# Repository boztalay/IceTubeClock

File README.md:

IceTubeClock
============

A clock with ice tubes for its display

Milling the enclosure:

Milling the base PCB:

Drilling the base PCB:

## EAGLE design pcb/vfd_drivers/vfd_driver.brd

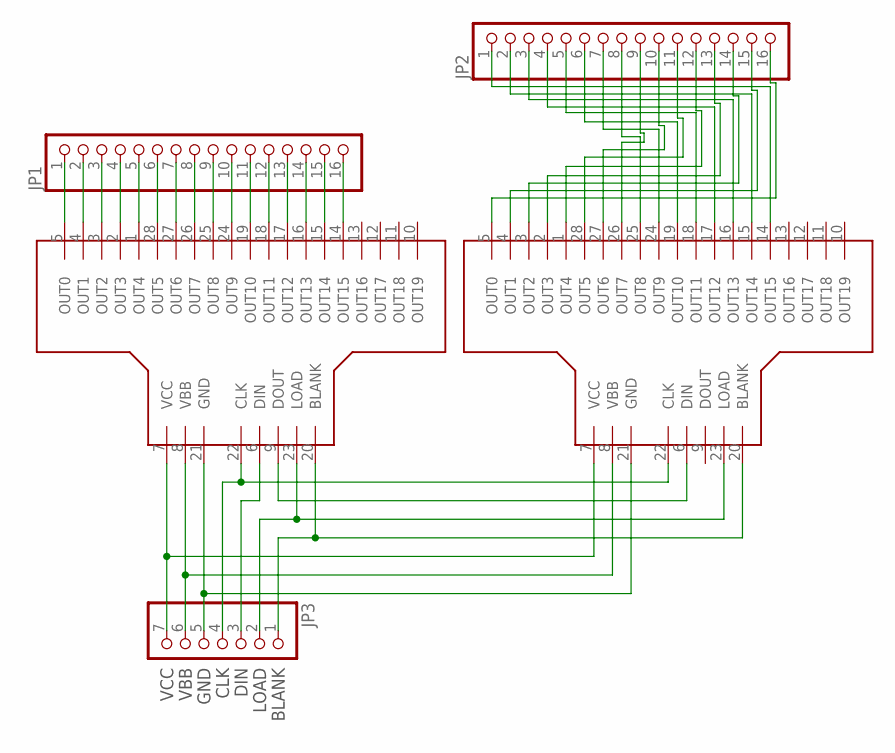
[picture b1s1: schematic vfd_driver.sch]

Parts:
JP1, JP2: PINHD-1X16; 1X16
JP3: PINHD-1X7; 1X07
U$1, U$2: MAX6921/31; TSSOP-28

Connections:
BLANK: JP3.1, U$1.20 (BLANK), U$2.20 (BLANK)
CLK: JP3.4, U$1.22 (CLK), U$2.22 (CLK)
DIN: JP3.3, U$1.6 (DIN)
DINOUT: U$1.9 (DOUT), U$2.6 (DIN)
GND: JP3.5, U$1.21 (GND), U$2.21 (GND)
LOAD: JP3.2, U$1.23 (LOAD), U$2.23 (LOAD)
unnamed: JP2.1, U$2.14 (OUT15)
unnamed: JP2.2, U$2.15 (OUT14)
unnamed: JP2.3, U$2.16 (OUT13)
unnamed: JP2.4, U$2.17 (OUT12)
unnamed: JP2.5, U$2.18 (OUT11)
unnamed: JP2.6, U$2.19 (OUT10)
unnamed: JP2.7, U$2.24 (OUT9)
unnamed: JP2.8, U$2.25 (OUT8)
unnamed: JP2.9, U$2.26 (OUT7)
unnamed: JP2.10, U$2.27 (OUT6)
unnamed: JP2.11, U$2.28 (OUT5)
unnamed: JP2.12, U$2.1 (OUT4)
unnamed: JP2.13, U$2.2 (OUT3)
unnamed: JP2.14, U$2.3 (OUT2)
unnamed: JP2.15, U$2.4 (OUT1)
unnamed: JP2.16, U$2.5 (OUT0)
unnamed: JP1.16, U$1.14 (OUT15)
unnamed: JP1.15, U$1.15 (OUT14)
unnamed: JP1.14, U$1.16 (OUT13)
unnamed: JP1.13, U$1.17 (OUT12)
unnamed: JP1.12, U$1.18 (OUT11)
unnamed: JP1.11, U$1.19 (OUT10)
unnamed: JP1.10, U$1.24 (OUT9)
unnamed: JP1.9, U$1.25 (OUT8)
unnamed: JP1.8, U$1.26 (OUT7)
unnamed: JP1.7, U$1.27 (OUT6)
unnamed: JP1.6, U$1.28 (OUT5)
unnamed: JP1.5, U$1.1 (OUT4)
unnamed: JP1.4, U$1.2 (OUT3)
unnamed: JP1.3, U$1.3 (OUT2)
unnamed: JP1.2, U$1.4 (OUT1)
unnamed: JP1.1, U$1.5 (OUT0)
VBB: JP3.6, U$1.8 (VBB), U$2.8 (VBB)
VCC: JP3.7, U$1.7 (VCC), U$2.7 (VCC)

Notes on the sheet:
VCC
VBB
GND
CLK
DIN
LOAD
BLANK

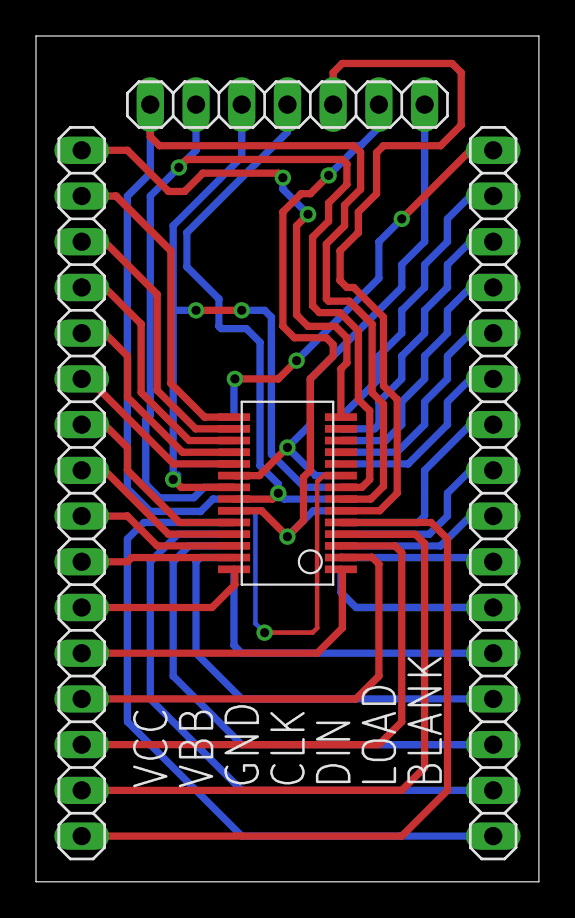
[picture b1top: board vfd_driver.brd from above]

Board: 2 copper layers, 27.9 x 47.0 mm, 5 parts (1 on the bottom side), 40 nets.

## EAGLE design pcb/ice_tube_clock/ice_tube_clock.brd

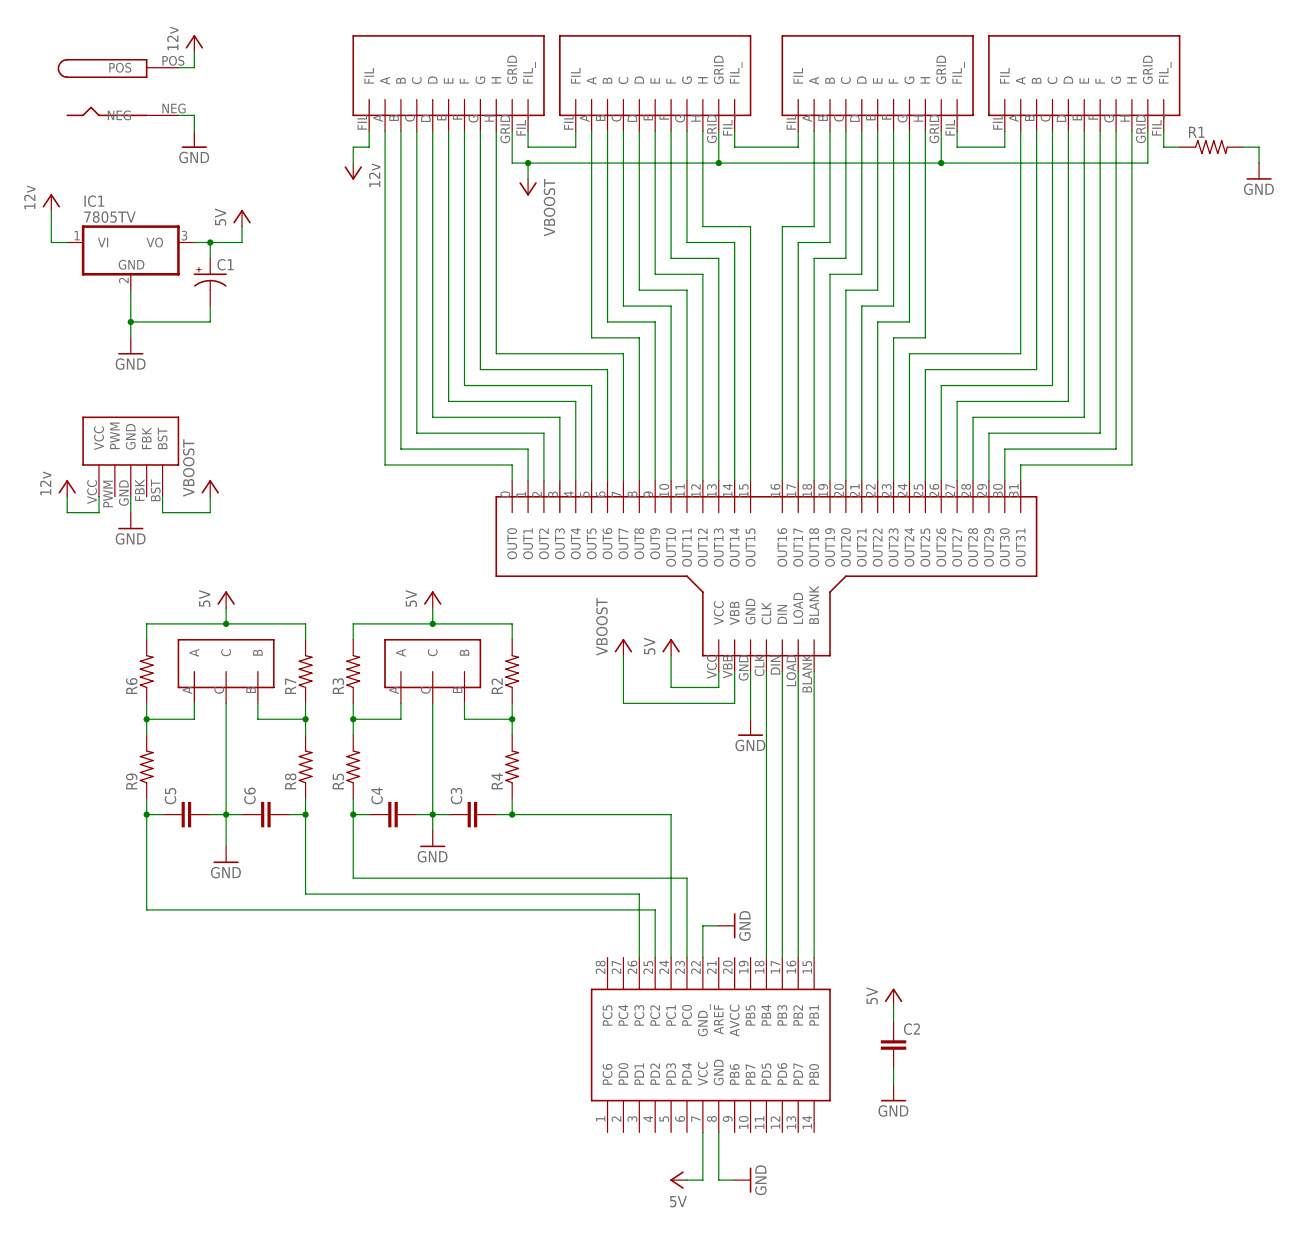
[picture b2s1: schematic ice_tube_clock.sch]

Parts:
C1: CAP_POLPTH1; CPOL-RADIAL-100UF-25V
C2, C3, C4, C5, C6: 0.1UF-50V-20%(PTH)KIT-EZ; CAP-PTH-SMALL-KIT
IC1: 7805TV; TO220V
R1, R2, R3, R4, R5, R6, R7, R8, R9: R-US_0204/7; 0204/7
U$1: ATMEGA168-DIP28; DIP28
U$2: IV11-BOOST-SUPPLY
U$3, U$4, U$5, U$6: IV-11-CARRIER
U$7: PJ-037A
U$8: VFD-DRIVER-CARRIER
U$9, U$10: PEL12S

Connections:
+5V: C1.1 (+), C2.1, IC1.3 (VO), R2.2, R3.2, R6.2, R7.2, U$1.7 (VCC), U$8.VCC
+12V: IC1.1 (VI), U$2.VCC, U$3.FIL, U$7.POS
ET: C4.1, R5.1, U$1.23 (PC0)
GND: C1.2 (-), C2.2, C3.1, C4.2, C5.2, C6.1, IC1.2 (GND), R1.2, U$1.8 (GND), U$1.22 (GND_), U$2.GND, U$7.NEG, U$8.GND, U$9.C, U$10.C
unnamed: U$3.FIL_, U$4.FIL
unnamed: U$4.FIL_, U$5.FIL
unnamed: U$5.FIL_, U$6.FIL
unnamed: U$3.A, U$8.0 (OUT0)
unnamed: U$3.B, U$8.1 (OUT1)
unnamed: U$3.C, U$8.2 (OUT2)
unnamed: U$3.D, U$8.3 (OUT3)
unnamed: U$3.E, U$8.4 (OUT4)
unnamed: U$3.F, U$8.5 (OUT5)
unnamed: U$3.G, U$8.6 (OUT6)
unnamed: U$3.H, U$8.7 (OUT7)
unnamed: U$4.A, U$8.8 (OUT8)
unnamed: U$4.B, U$8.9 (OUT9)
unnamed: U$4.C, U$8.10 (OUT10)
unnamed: U$4.D, U$8.11 (OUT11)
unnamed: U$4.E, U$8.12 (OUT12)
unnamed: U$4.F, U$8.13 (OUT13)
unnamed: U$4.G, U$8.14 (OUT14)
unnamed: U$4.H, U$8.15 (OUT15)
unnamed: U$6.H, U$8.31 (OUT31)
unnamed: U$6.G, U$8.30 (OUT30)
unnamed: U$6.F, U$8.29 (OUT29)
unnamed: U$6.E, U$8.28 (OUT28)
unnamed: U$6.D, U$8.27 (OUT27)
unnamed: U$6.C, U$8.26 (OUT26)
unnamed: U$6.B, U$8.25 (OUT25)
unnamed: U$6.A, U$8.24 (OUT24)
unnamed: U$5.H, U$8.23 (OUT23)
unnamed: U$5.G, U$8.22 (OUT22)
unnamed: U$5.F, U$8.21 (OUT21)
unnamed: U$5.E, U$8.20 (OUT20)
unnamed: U$5.D, U$8.19 (OUT19)
unnamed: U$5.C, U$8.18 (OUT18)
unnamed: U$5.B, U$8.17 (OUT17)
unnamed: U$5.A, U$8.16 (OUT16)
unnamed: R1.1, U$6.FIL_
unnamed: U$1.15 (PB1), U$8.BLANK
unnamed: U$1.16 (PB2), U$8.LOAD
unnamed: U$1.17 (PB3), U$8.DIN
unnamed: U$1.18 (PB4), U$8.CLK
unnamed: C3.2, R4.1, U$1.24 (PC1)
unnamed: R3.1, R5.2, U$10.A
unnamed: R6.1, R9.2, U$9.A
unnamed: R7.1, R8.2, U$9.B
unnamed: R2.1, R4.2, U$10.B
unnamed: C5.1, R9.1, U$1.25 (PC2)
unnamed: C6.2, R8.1, U$1.26 (PC3)
VBOOST: U$2.BST, U$3.GRID, U$4.GRID, U$5.GRID, U$6.GRID, U$8.VBB

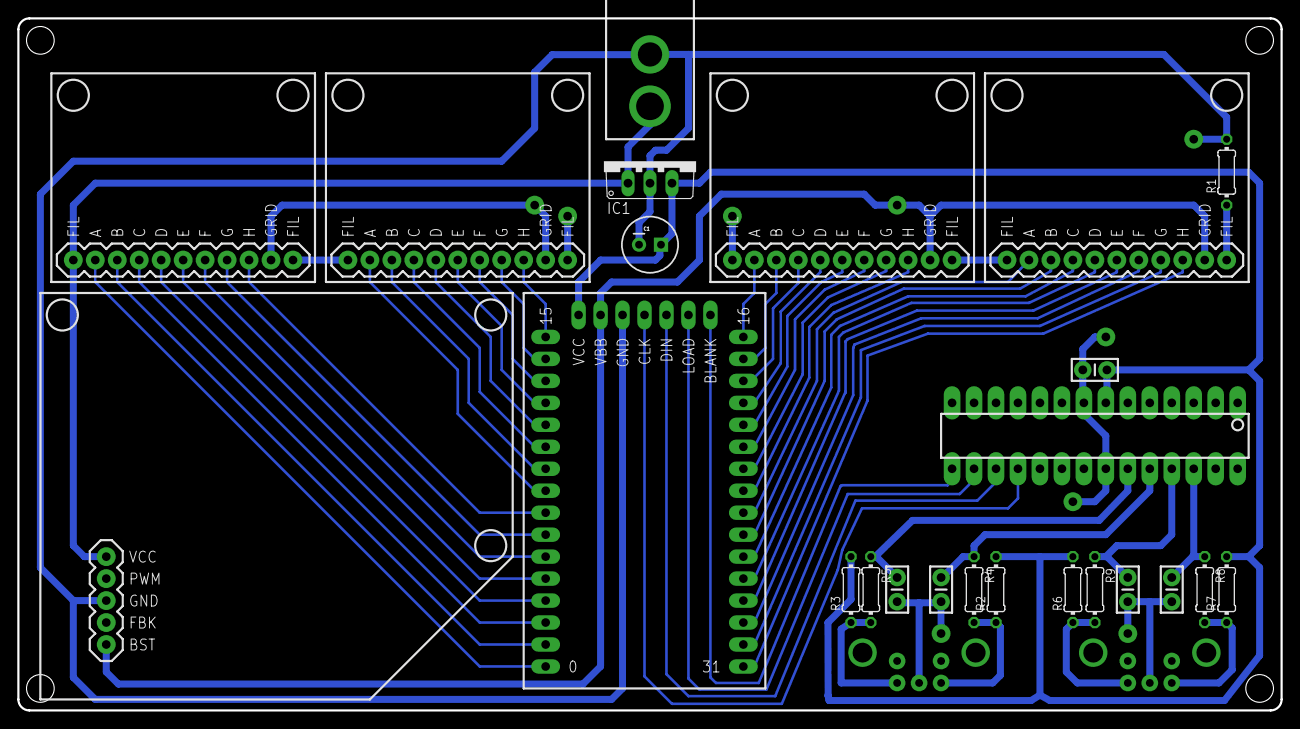
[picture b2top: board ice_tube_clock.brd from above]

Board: 2 copper layers, 146.1 x 80.0 mm, 26 parts (0 on the bottom side), 52 nets.

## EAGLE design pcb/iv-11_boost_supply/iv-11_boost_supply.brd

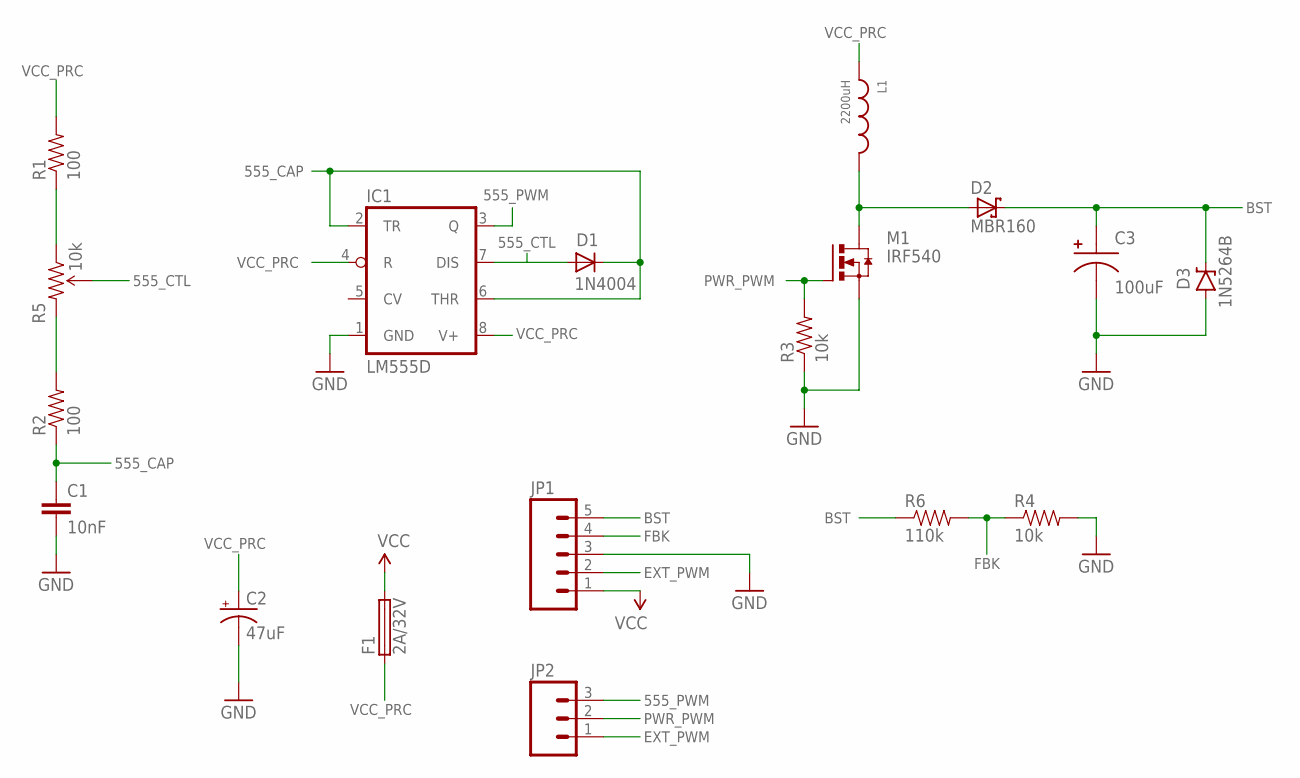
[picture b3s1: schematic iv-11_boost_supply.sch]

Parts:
C1: 10nF; 1206
C2: 47uF; CPOL-RADIAL-100UF-25V
C3: 100uF; POLAR-CAP-PTH-10MM
D1: 1N4004; DO41-10
D2: MBR160; DO41-10
D3: 1N5264B; DIODE-ZENER
F1: 2A/32V; 1AG-1/4X5/8-FUSE
IC1: LM555D; SO08
JP1: M05LOCK; 1X05_LOCK
JP2: M03LOCK; 1X03_LOCK
L1: 2200uH; INDUCTOR-PTH-13MM
M1: IRF540; D2PACK
R1, R2: 100; 1206
R3, R4: 10k; 1206
R5: 10k; TRIMPOT-5MM-V2
R6: 110k; 1206

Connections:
555_CAP: C1.1, D1.C, IC1.2 (TR), IC1.6 (THR), R2.1
555_CTL: D1.A, IC1.7 (DIS), R5.B (WIPER)
555_PWM: IC1.3 (Q), JP2.3
BST: C3.A, D2.C, D3.P$1 (C), JP1.5, R6.1
EXT_PWM: JP1.2, JP2.1
FBK: JP1.4, R4.1, R6.2
GND: C1.2, C2.2 (-), C3.B, D3.P$2 (A), IC1.1 (GND), JP1.3, M1.3 (S), R3.1, R4.2
unnamed: R1.1, R5.A (CCW)
unnamed: R2.2, R5.C (CW)
unnamed: D2.A, L1.B, M1.2 (D)
PWR_PWM: JP2.2, M1.1 (G), R3.2
VCC: F1.P$3 (2), F1.P$4 (2), JP1.1
VCC_PRC: C2.1 (+), F1.P$1 (1), F1.P$2 (1), IC1.4 (R), IC1.8 (V+), L1.A, R1.2

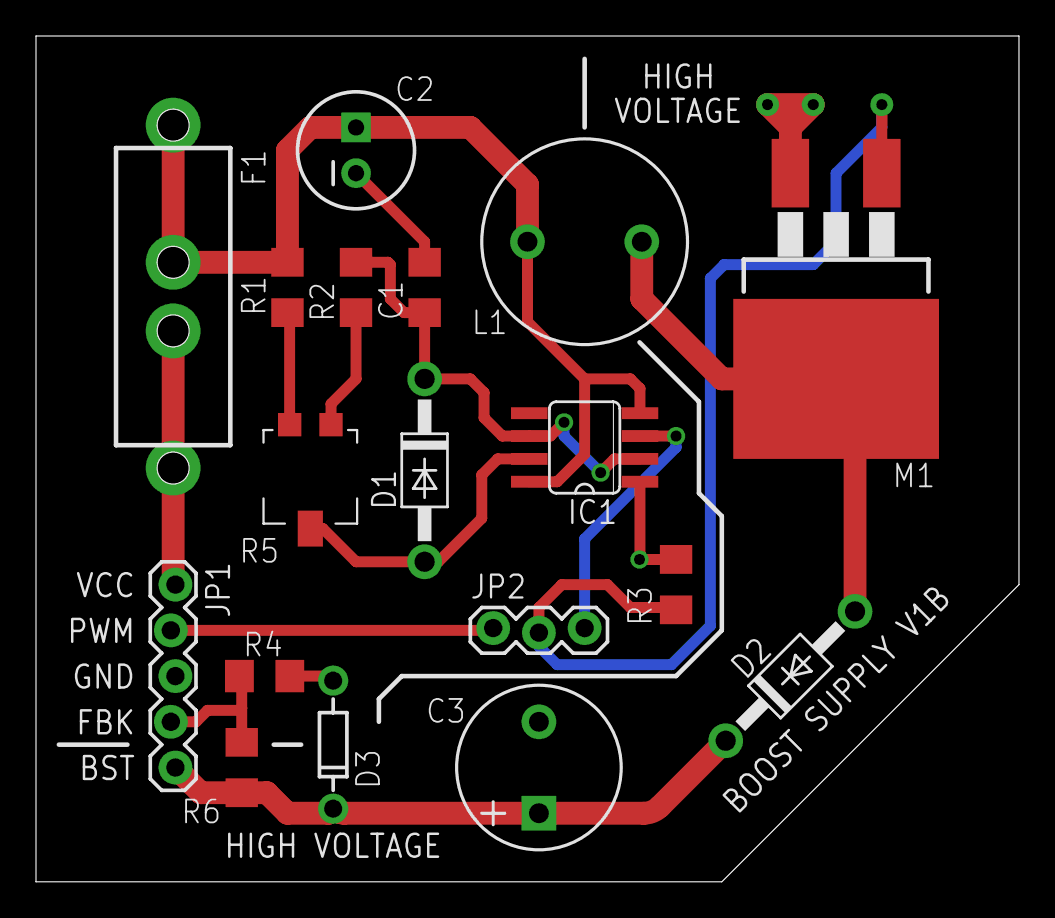
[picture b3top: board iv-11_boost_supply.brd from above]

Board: 2 copper layers, 54.6 x 47.0 mm, 18 parts (0 on the bottom side), 13 nets.

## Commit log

2014-04-14 Starting the BOM to order some initial parts
2014-04-15 Full BOM (so far)
2014-04-26 Tweaking the PWM stuff
2014-04-26 Cleaned up the code, got the boost voltage monitor/feedback loop working
2014-04-27 Working on a breakout board for IV-11 tubes
2014-04-27 New layout for the IV-11 breakout, fixed the drill size
2014-04-27 Generated Gerber files and sent it off for fabrication
2014-04-28 Things get weird with more than one tube connected
2014-05-06 Working on interfacing with the tube drivers
2014-05-07 Adding some datasheets
2014-05-08 Tweaking some values for the boost supply)
2014-05-08 Cleaned up some files
2014-05-22 Trying desperately to get Timer2 to give me some PWM
2014-11-15 Starting on the boost supply board, finding parts
2014-11-15 Got all the parts in place, also found some more parts
2014-11-15 Not sure what changed here, EAGLE is fun
2014-11-16 Made a fuse part, got the rest of the parts in place
2014-11-19 Did most of the board layout, found more parts to order
2014-12-22 Cleaned up the board layout, need the parts to test it out on paper
2014-12-22 Not entirely sure what changed here, but Eagle wanted to save things
2015-02-05 Finalizing the layout
2015-02-05 First draft of routing
2015-02-09 Making component names more visible on the board
2015-02-09 Adding some labeling to the boost supply board
2015-02-12 Tested the layout for the boost supply board, specified that it's rev A
2015-02-12 Working on rev B of the boost supply board
2015-02-12 Finished up rev B of the boost supply board, but the layout still needs to be tested
2015-02-12 Made a pdf for the current boost supply board
2015-02-12 Turned layers on
2016-04-04 Starting on the main board
2016-04-04 More big parts
2016-04-06 Starting on basic layout of the board
2016-04-12 I thought I committed all this stuff
2016-04-12 Knobs
2016-04-18 Finalized the VFD driver carrier board
2016-04-19 Getting the toolchain set up again
2016-04-19 Added a gitignore for the AVR stuff
2016-04-19 Cleaning out stuff related to active power supply regulation, won't need that
2016-04-19 Testing number displays
2016-04-19 Add support for a real time clock based on an external oscillator
2016-04-19 Changed it to count minutes instead of seconds
2016-04-23 First draft of knob-reading firmware, haven't tested it yet
2016-04-23 Messing around with the knob-reading code
2016-04-26 Getting the firmware to work with the PCB, cleaning it up
2020-06-18 Add some images
2020-06-18 README updates
2020-06-18 Resize the images

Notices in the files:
parts and their libraries:
SparkFun-Passives: Licensing: Creative Commons ShareAlike 4.0 International - https://creativecommons.org/licenses/by-sa/4.0
